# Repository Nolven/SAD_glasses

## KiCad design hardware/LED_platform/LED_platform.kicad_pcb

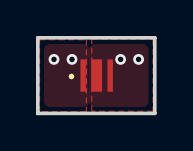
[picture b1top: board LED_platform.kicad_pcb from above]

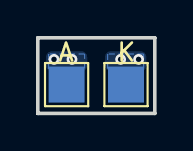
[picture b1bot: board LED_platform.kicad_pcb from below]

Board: 2 copper layers, 6.5 x 4.2 mm, 3 parts (2 on the bottom side), 2 nets, no tracks yet.

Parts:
A: A; TestPoint_Pad_2.0x2.0mm
K: K; TestPoint_Pad_2.0x2.0mm
LED1: L1C1-CYN1000000000; L1C1CYN1000000000

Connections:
unnamed: A.1 (1_1), LED1.2 (A), LED1.3 (HEAT_PAD)
unnamed: K.1 (1_1), LED1.1 (K)

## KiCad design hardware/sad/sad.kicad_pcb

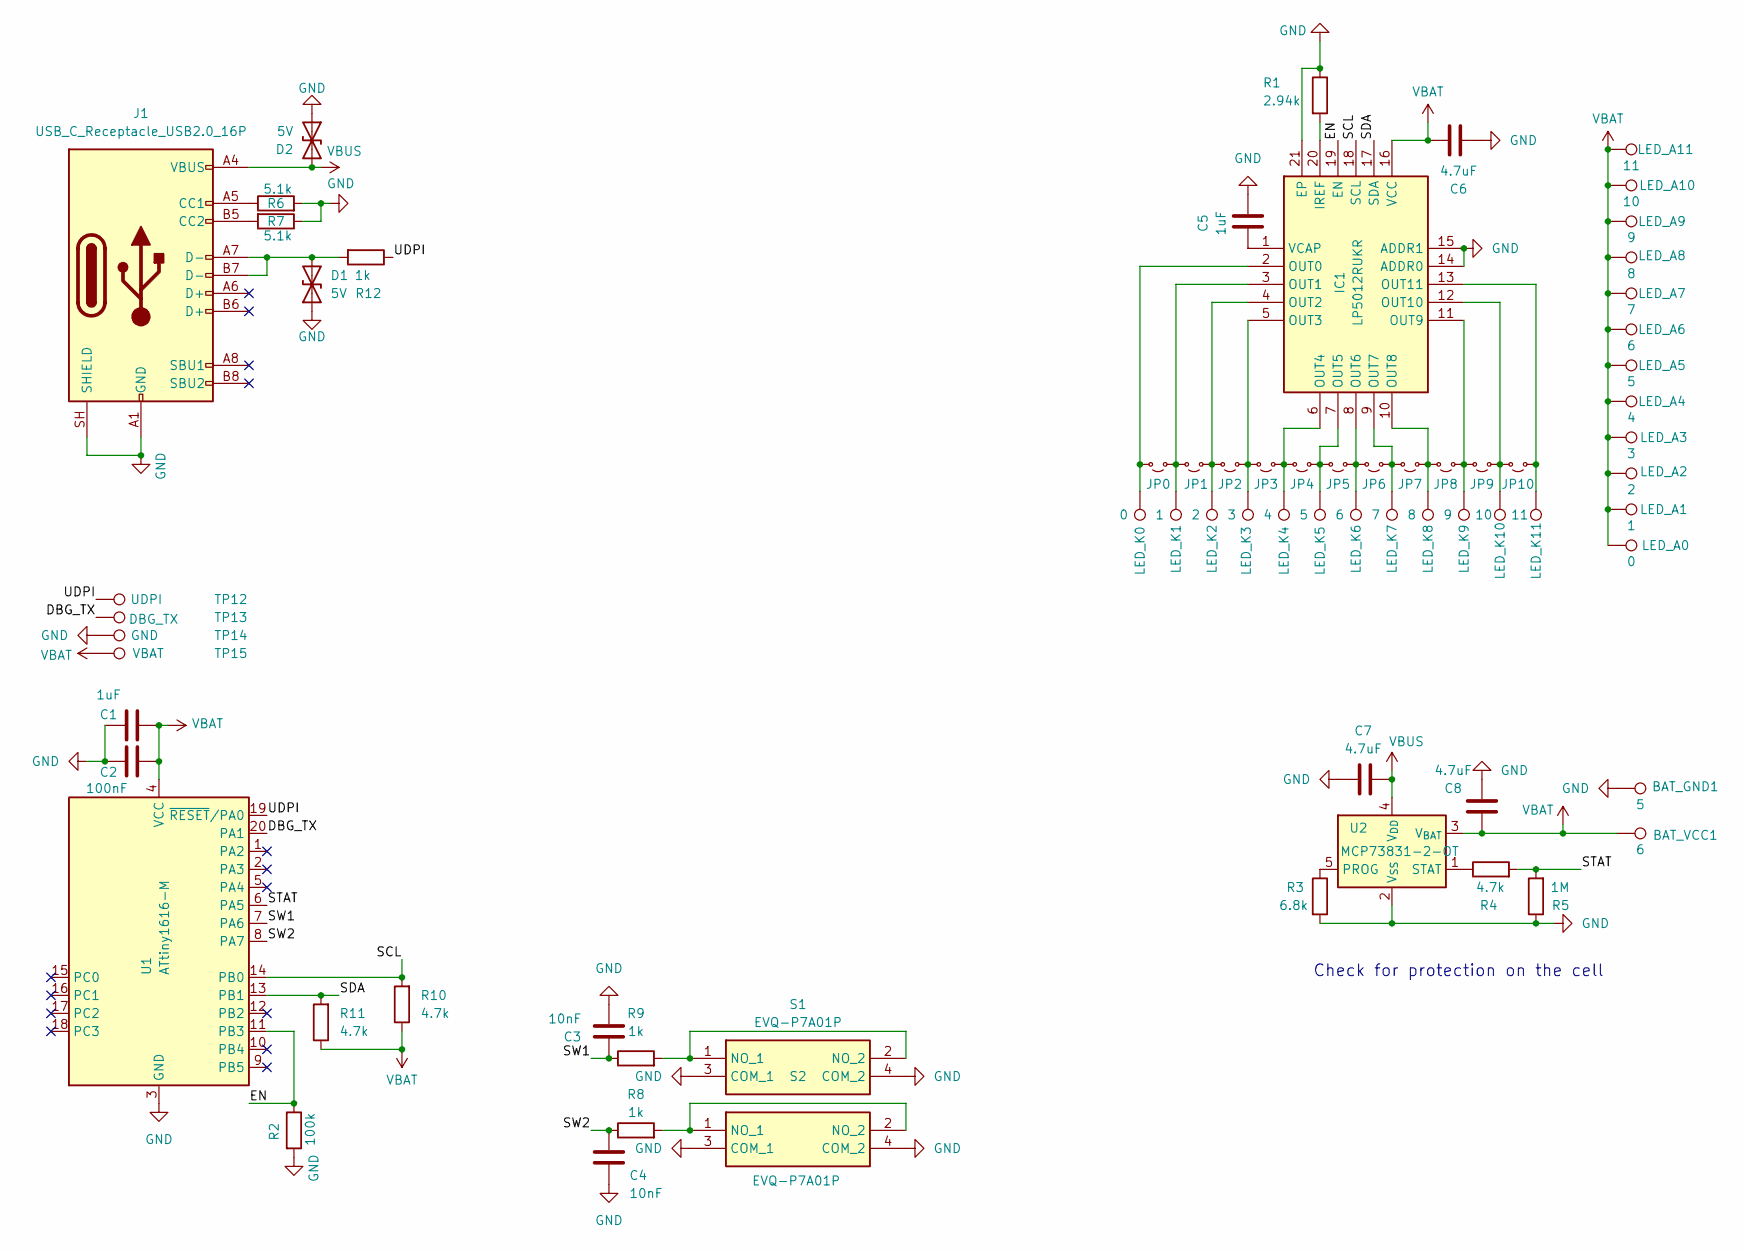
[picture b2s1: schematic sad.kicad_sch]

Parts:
BAT_GND1: 5; SolderWirePad_1x01_SMD_1x2mm
BAT_VCC1: 6; SolderWirePad_1x01_SMD_1x2mm
C1, C5: 1uF; C_0402_1005Metric_Pad0.74x0.62mm_HandSolder
C2: 100nF; C_0402_1005Metric_Pad0.74x0.62mm_HandSolder
C3, C4: 10nF; C_0402_1005Metric_Pad0.74x0.62mm_HandSolder
C6, C7, C8: 4.7uF; C_0603_1608Metric_Pad1.08x0.95mm_HandSolder
D1, D2: 5V; D_SOD-882
IC1: LP5012RUKR; QFN40P300X300X80-21N-D; Manufacturer_Part_Number LP5012RUKR; Mouser Part Number 595-LP5012RUKR
J1: USB_C_Receptacle_USB2.0_16P; USB_C_Receptacle_GCT_USB4105-xx-A_16P_TopMnt_Horizontal
JP0, JP1, JP2, JP3, JP4, JP5, JP6, JP7, JP8, JP9, JP10: R_0402_1005Metric_Pad0.72x0.64mm_HandSolder
LED_A0: 0; SolderWirePad_1x01_SMD_1x2mm
LED_A1: 1; SolderWirePad_1x01_SMD_1x2mm
LED_A2: 2; SolderWirePad_1x01_SMD_1x2mm
LED_A3: 3; SolderWirePad_1x01_SMD_1x2mm
LED_A4: 4; SolderWirePad_1x01_SMD_1x2mm
LED_A5: 5; SolderWirePad_1x01_SMD_1x2mm
LED_A6: 6; SolderWirePad_1x01_SMD_1x2mm
LED_A7: 7; SolderWirePad_1x01_SMD_1x2mm
LED_A8: 8; SolderWirePad_1x01_SMD_1x2mm
LED_A9: 9; SolderWirePad_1x01_SMD_1x2mm
LED_A10: 10; SolderWirePad_1x01_SMD_1x2mm
LED_A11: 11; SolderWirePad_1x01_SMD_1x2mm
LED_K0: 0; SolderWirePad_1x01_SMD_1x2mm
LED_K1: 1; SolderWirePad_1x01_SMD_1x2mm
LED_K2: 2; SolderWirePad_1x01_SMD_1x2mm
LED_K3: 3; SolderWirePad_1x01_SMD_1x2mm
LED_K4: 4; SolderWirePad_1x01_SMD_1x2mm
LED_K5: 5; SolderWirePad_1x01_SMD_1x2mm
LED_K6: 6; SolderWirePad_1x01_SMD_1x2mm
LED_K7: 7; SolderWirePad_1x01_SMD_1x2mm
LED_K8: 8; SolderWirePad_1x01_SMD_1x2mm
LED_K9: 9; SolderWirePad_1x01_SMD_1x2mm
LED_K10: 10; SolderWirePad_1x01_SMD_1x2mm
LED_K11: 11; SolderWirePad_1x01_SMD_1x2mm
R1: 2.94k; R_0402_1005Metric_Pad0.72x0.64mm_HandSolder
R2: 100k; R_0402_1005Metric_Pad0.72x0.64mm_HandSolder
R3: 6.8k; R_0402_1005Metric_Pad0.72x0.64mm_HandSolder
R4, R10, R11: 4.7k; R_0402_1005Metric_Pad0.72x0.64mm_HandSolder
R5: 1M; R_0402_1005Metric_Pad0.72x0.64mm_HandSolder
R6, R7: 5.1k; R_0402_1005Metric_Pad0.72x0.64mm_HandSolder
R8, R9, R12: 1k; R_0402_1005Metric_Pad0.72x0.64mm_HandSolder
S1, S2: EVQ-P7A01P; EVQP7J01P; Manufacturer_Part_Number EVQ-P7A01P; Mouser Part Number 667-EVQP7A01P
TP12: UDPI; SolderWirePad_1x01_SMD_1x2mm
TP13: DBG_TX; SolderWirePad_1x01_SMD_1x2mm
TP14: GND; SolderWirePad_1x01_SMD_1x2mm
TP15: VBAT; SolderWirePad_1x01_SMD_1x2mm
U1: ATtiny1616-M; VQFN-20-1EP_3x3mm_P0.4mm_EP1.7x1.7mm
U2: MCP73831-2-OT; SOT-23-5

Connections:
/DBG_TX: TP13.1, U1.20 (PA1); also elsewhere on the board
/EN: IC1.19 (EN), R2.1, U1.11 (PB3)
/SCL: IC1.18 (SCL), R10.2, U1.14 (PB0)
/SDA: IC1.17 (SDA), R11.2, U1.13 (PB1)
/STAT: R4.2, R5.2, U1.6 (PA5)
/SW1: C3.1, R9.1, U1.7 (PA6)
/SW2: C4.1, R8.1, U1.8 (PA7)
/UDPI: R12.1, TP12.1, U1.19 (~RESET/PA0); also elsewhere on the board
GND: BAT_GND1.1, C1.2, C2.1, C3.2, C4.2, C5.2, C6.1, C7.1, C8.2, D1.1 (A1), D2.1 (A1), IC1.14 (ADDR0), IC1.15 (ADDR1), IC1.21 (EP), J1.A1 (GND), J1.A12 (GND), J1.B1 (GND), J1.B12 (GND), J1.SH (SHIELD), R1.1, R2.2, R3.2, R5.1, R6.2, R7.1, S1.3 (COM_1), S1.4 (COM_2), S2.3 (COM_1), S2.4 (COM_2), TP14.1, U1.3 (GND), U1.21 (GND), U2.2 (V_{SS}); also elsewhere on the board
unnamed: D1.2 (A2), J1.A7 (D-), J1.B7 (D-), R12.2
unnamed: IC1.20 (IREF), R1.2
unnamed: IC1.2 (OUT0), JP0.2 (B), LED_K0.1 (1_1)
unnamed: IC1.3 (OUT1), JP0.1 (A), JP1.2 (B), LED_K1.1 (1_1)
unnamed: IC1.4 (OUT2), JP1.1 (A), JP2.1 (A), LED_K2.1 (1_1)
unnamed: IC1.5 (OUT3), JP2.2 (B), JP3.2 (B), LED_K3.1 (1_1)
unnamed: IC1.6 (OUT4), JP3.1 (A), JP4.2 (B), LED_K4.1 (1_1)
unnamed: IC1.7 (OUT5), JP4.1 (A), JP5.2 (B), LED_K5.1 (1_1)
unnamed: IC1.8 (OUT6), JP5.1 (A), JP6.2 (B), LED_K6.1 (1_1)
unnamed: IC1.9 (OUT7), JP6.1 (A), JP7.2 (B), LED_K7.1 (1_1)
unnamed: IC1.10 (OUT8), JP7.1 (A), JP8.2 (B), LED_K8.1 (1_1)
unnamed: IC1.11 (OUT9), JP8.1 (A), JP9.2 (B), LED_K9.1 (1_1)
unnamed: IC1.12 (OUT10), JP9.1 (A), JP10.2 (B), LED_K10.1 (1_1)
unnamed: IC1.13 (OUT11), JP10.1 (A), LED_K11.1 (1_1)
unnamed: C5.1, IC1.1 (VCAP)
unnamed: J1.A5 (CC1), R6.1
unnamed: J1.B5 (CC2), R7.2
unnamed: R9.2, S1.1 (NO_1), S1.2 (NO_2)
unnamed: R8.2, S2.1 (NO_1), S2.2 (NO_2)
unnamed: R3.1, U2.5 (PROG)
unnamed: R4.1, U2.1 (STAT)
VBAT: BAT_VCC1.1, C1.1, C2.2, C6.2, C8.1, IC1.16 (VCC), LED_A0.1 (1_1), LED_A1.1 (1_1), LED_A2.1 (1_1), LED_A3.1 (1_1), LED_A4.1 (1_1), LED_A5.1 (1_1), LED_A6.1 (1_1), LED_A7.1 (1_1), LED_A8.1 (1_1), LED_A9.1 (1_1), LED_A10.1 (1_1), LED_A11.1 (1_1), R10.1, R11.1, TP15.1, U1.4 (VCC), U2.3 (V_{BAT}); also elsewhere on the board
VBUS: C7.2, D2.2 (A2), J1.A4 (VBUS), J1.A9 (VBUS), J1.B4 (VBUS), J1.B9 (VBUS), U2.4 (V_{DD})

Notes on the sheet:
Check for protection on the cell

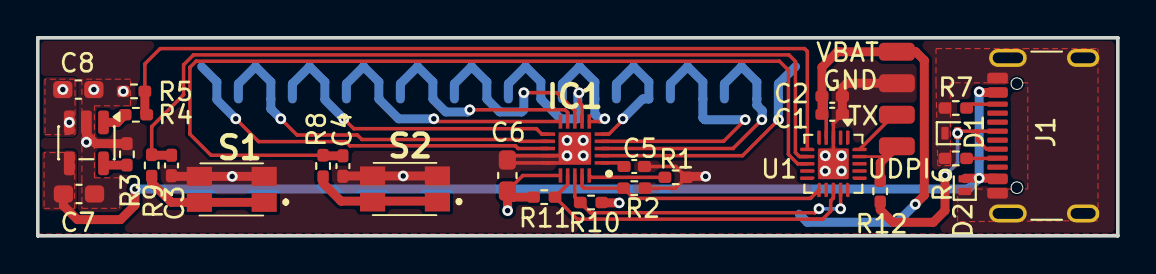
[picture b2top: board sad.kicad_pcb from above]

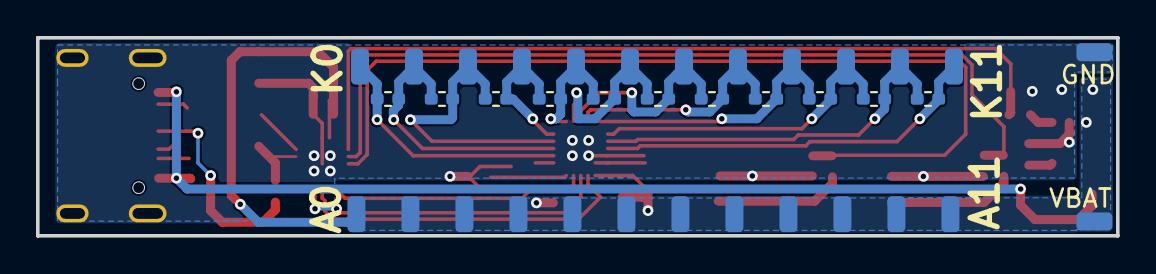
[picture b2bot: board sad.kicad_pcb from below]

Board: 2 copper layers, 60.0 x 11.0 mm, 69 parts (37 on the bottom side), 32 nets.

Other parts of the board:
GND: GND; SolderWirePad_1x01_SMD_1x2mm
GND#2: 5; SolderWirePad_1x01_SMD_1x2mm
TX: DBG_TX; SolderWirePad_1x01_SMD_1x2mm
UDPI: UDPI; SolderWirePad_1x01_SMD_1x2mm
VBAT: VBAT; SolderWirePad_1x01_SMD_1x2mm
VBAT#2: 6; SolderWirePad_1x01_SMD_1x2mm

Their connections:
/DBG_TX: TX.1 (1_1); also elsewhere on the board
/UDPI: UDPI.1 (1_1); also elsewhere on the board
GND: GND.1 (1_1), GND#2.1 (1_1); also elsewhere on the board
VBAT: VBAT.1 (1_1), VBAT#2.1 (1_1); also elsewhere on the board

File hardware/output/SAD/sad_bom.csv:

Manufacturer Part Number,Manufacturer,Description,References,Qty per board,Order Qty
LP5012RUKR,Texas Instruments,12-ch I2C LED driver WQFN-20 3x3,IC1,1,3
ATTINY1616-MNR,Microchip,AVR MCU 16KB VQFN-20 3x3,U1,1,3
MCP73831T-2ACI/OT,Microchip,Li-ion charger 4.20V SOT-23-5,U2,1,3
TPD1E10B06DPYR,Texas Instruments,ESD TVS 5.5V bidirectional 0402 X1SON (SOD-882 size),"D1, D2",2,6
EVQ-P7A01P,Panasonic,Side-push tact switch 3.5x2.9mm 2.2N,"S1, S2",2,6
USB4105-GF-A,GCT,USB-C 2.0 16P top-mount receptacle 0.95mm stakes,J1,1,3
L1C1-CYN1000000000,Lumileds,LUXEON C Cyan 490-510nm 2x2mm,LED pads,12,15
CL05A105KP5NNNC,Samsung Electro-Mechanics,1uF 10V X5R 0402 (alt: TDK C1005X5R1A105K050BC),"C1, C5",2,10
GRM155R71C104KA88D,Murata,100nF 16V X7R 0402,C2,1,10
GRM155R71H103KA88D,Murata,10nF 50V X7R 0402,"C3, C4",2,10
CL10A475KO8NNNC,Samsung Electro-Mechanics,4.7uF 16V X5R 0603 (alt: TDK C1608X5R1C475K080AC),"C6, C7, C8 (+ anode bulk cap)",4,15
RC0402FR-072K94L,Yageo,2.94k 1% 0402,R1,1,10
RC0402FR-07100KL,Yageo,100k 1% 0402,R2,1,10
RC0402FR-076K8L,Yageo,6.8k 1% 0402,R3,1,10
RC0402FR-074K7L,Yageo,4.7k 1% 0402,"R4, R10, R11",3,10
RC0402FR-071ML,Yageo,1M 1% 0402,R5,1,10
RC0402FR-075K1L,Yageo,5.1k 1% 0402,"R6, R7",2,10
RC0402FR-071KL,Yageo,1k 1% 0402,"R8, R9, R12",3,10
